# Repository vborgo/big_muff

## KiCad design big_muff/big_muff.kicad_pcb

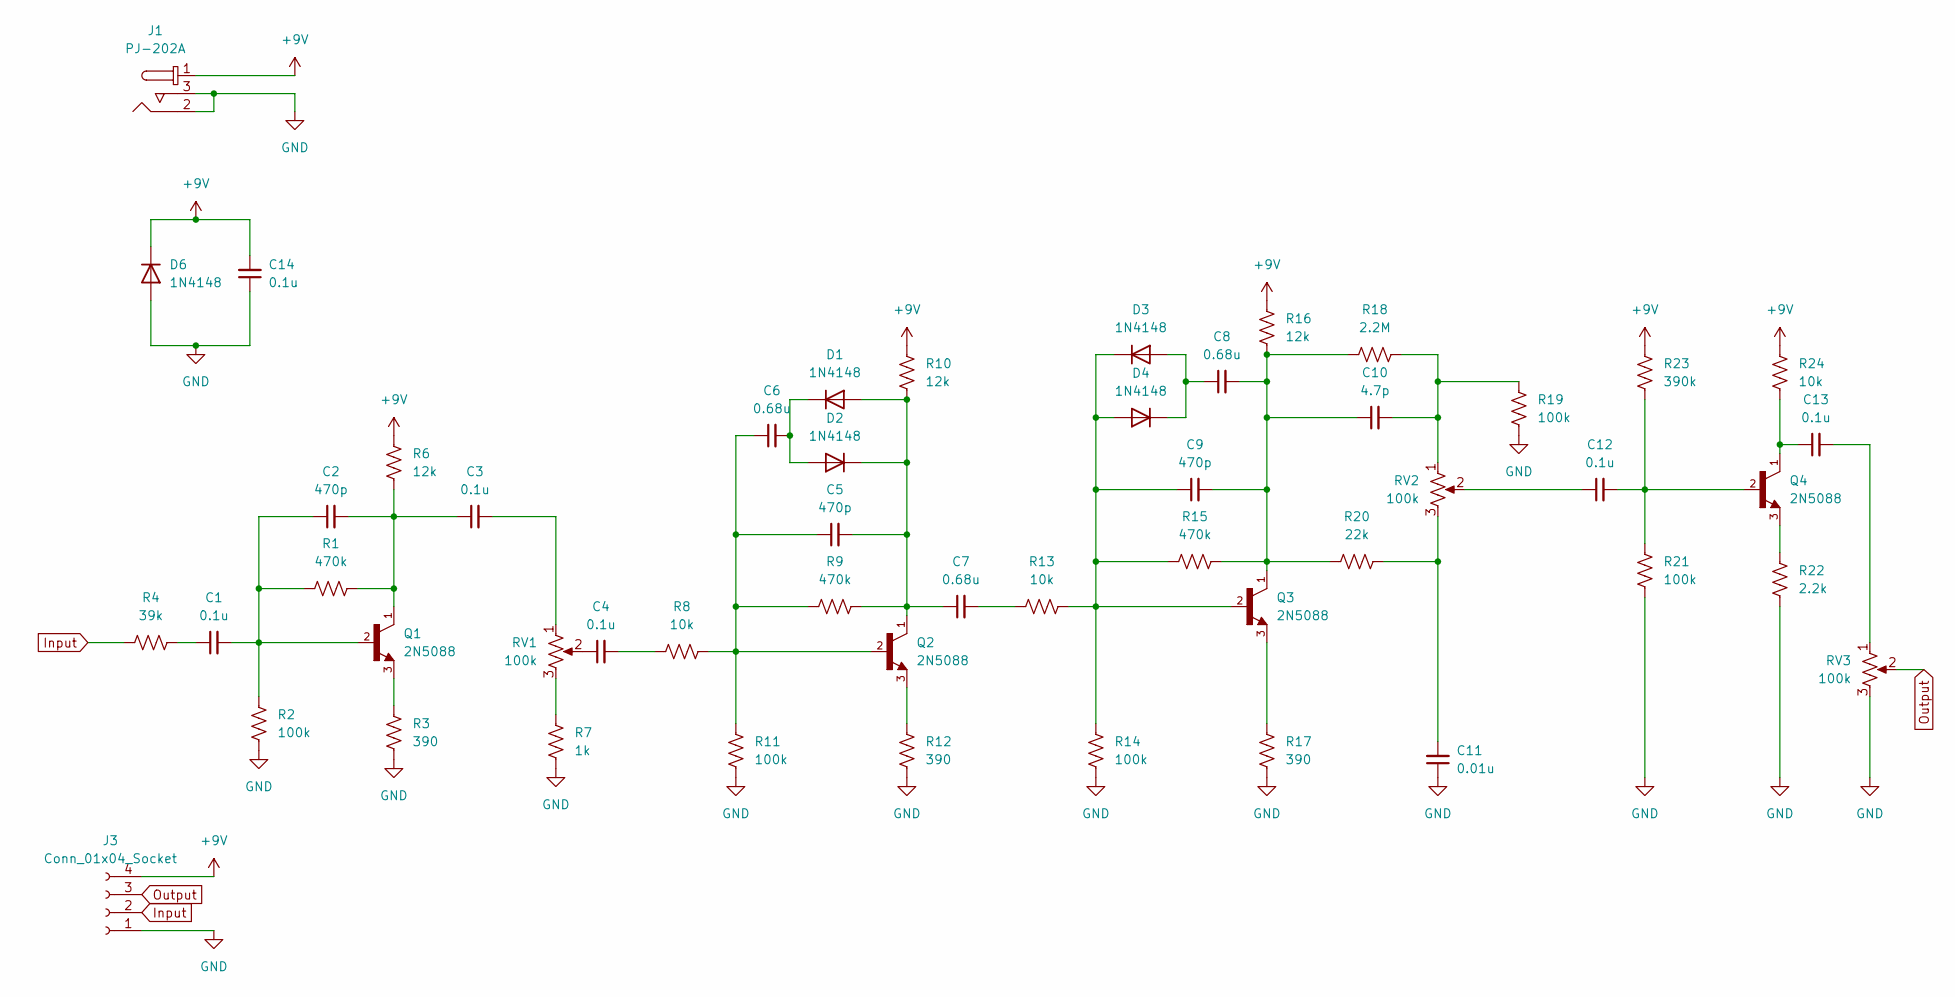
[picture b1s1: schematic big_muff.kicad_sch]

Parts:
C1, C3, C4, C12, C13, C14: 0.1u; C_Axial_L5.1mm_D3.1mm_P7.50mm_Horizontal
C2, C5, C9: 470p; C_Axial_L5.1mm_D3.1mm_P7.50mm_Horizontal
C6, C7, C8: 0.68u; C_Axial_L5.1mm_D3.1mm_P7.50mm_Horizontal
C10: 4.7p; C_Axial_L5.1mm_D3.1mm_P7.50mm_Horizontal
C11: 0.01u; C_Axial_L5.1mm_D3.1mm_P7.50mm_Horizontal
D1, D2, D3, D4, D6: 1N4148; D_DO-35_SOD27_P7.62mm_Horizontal
J1: PJ-202A; BarrelJack_GCT_DCJ200-10-A_Horizontal; MPN PJ-202A; Digi-Key_PN CP-202A-ND
J3: Conn_01x04_Socket; PinHeader_1x04_P2.00mm_Vertical
Q1, Q2, Q3, Q4: 2N5088; TO92
R1, R9, R15: 470k; R_Axial_DIN0204_L3.6mm_D1.6mm_P5.08mm_Horizontal
R2, R11, R14, R19, R21: 100k; R_Axial_DIN0204_L3.6mm_D1.6mm_P5.08mm_Horizontal
R3, R12, R17: 390; R_Axial_DIN0204_L3.6mm_D1.6mm_P5.08mm_Horizontal
R4: 39k; R_Axial_DIN0204_L3.6mm_D1.6mm_P5.08mm_Horizontal
R6, R10, R16: 12k; R_Axial_DIN0204_L3.6mm_D1.6mm_P5.08mm_Horizontal
R7: 1k; R_Axial_DIN0204_L3.6mm_D1.6mm_P5.08mm_Horizontal
R8, R13, R24: 10k; R_Axial_DIN0204_L3.6mm_D1.6mm_P5.08mm_Horizontal
R18: 2.2M; R_Axial_DIN0204_L3.6mm_D1.6mm_P5.08mm_Horizontal
R20: 22k; R_Axial_DIN0204_L3.6mm_D1.6mm_P5.08mm_Horizontal
R22: 2.2k; R_Axial_DIN0204_L3.6mm_D1.6mm_P5.08mm_Horizontal
R23: 390k; R_Axial_DIN0204_L3.6mm_D1.6mm_P5.08mm_Horizontal
RV1, RV2, RV3: 100k; Potentiometer_Bourns_PTV09A-1_Single_Vertical

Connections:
+9V: C14.2, D6.1 (K), J1.1, J3.4, R6.1, R10.2, R16.2, R23.1, R24.1
GND: C11.1, C14.1, D6.2 (A), J1.2, J1.3, J3.1, R2.2, R3.2, R7.2, R11.1, R12.1, R14.1, R17.1, R19.2, R21.2, R22.2, RV3.3
Input: J3.2, R4.2
unnamed: C1.1, R4.1
unnamed: C1.2, C2.1, Q1.2, R1.2, R2.1
unnamed: C2.2, C3.1, Q1.1, R1.1, R6.2
unnamed: C3.2, RV1.1
unnamed: C4.1, RV1.2
unnamed: C4.2, R8.1
unnamed: C5.1, C6.1, Q2.2, R8.2, R9.1, R11.2
unnamed: C7.2, R13.1
unnamed: C8.2, C9.2, C10.1, Q3.1, R15.2, R16.1, R18.2, R20.2
unnamed: C10.2, R18.1, R19.1, RV2.1
unnamed: C11.2, R20.1, RV2.3
unnamed: C12.1, RV2.2
unnamed: C12.2, Q4.2, R21.1, R23.2
unnamed: C13.1, Q4.1, R24.2
unnamed: C13.2, RV3.1
unnamed: C5.2, C7.1, D1.2 (A), D2.1 (K), Q2.1, R9.2, R10.1
unnamed: C6.2, D1.1 (K), D2.2 (A)
unnamed: C8.1, D3.2 (A), D4.1 (K)
unnamed: C9.1, D3.1 (K), D4.2 (A), Q3.2, R13.2, R14.2, R15.1
unnamed: Q1.3, R3.1
unnamed: Q2.3, R12.2
unnamed: Q3.3, R17.2
unnamed: Q4.3, R22.1
unnamed: R7.1, RV1.3
Output: J3.3, RV3.2

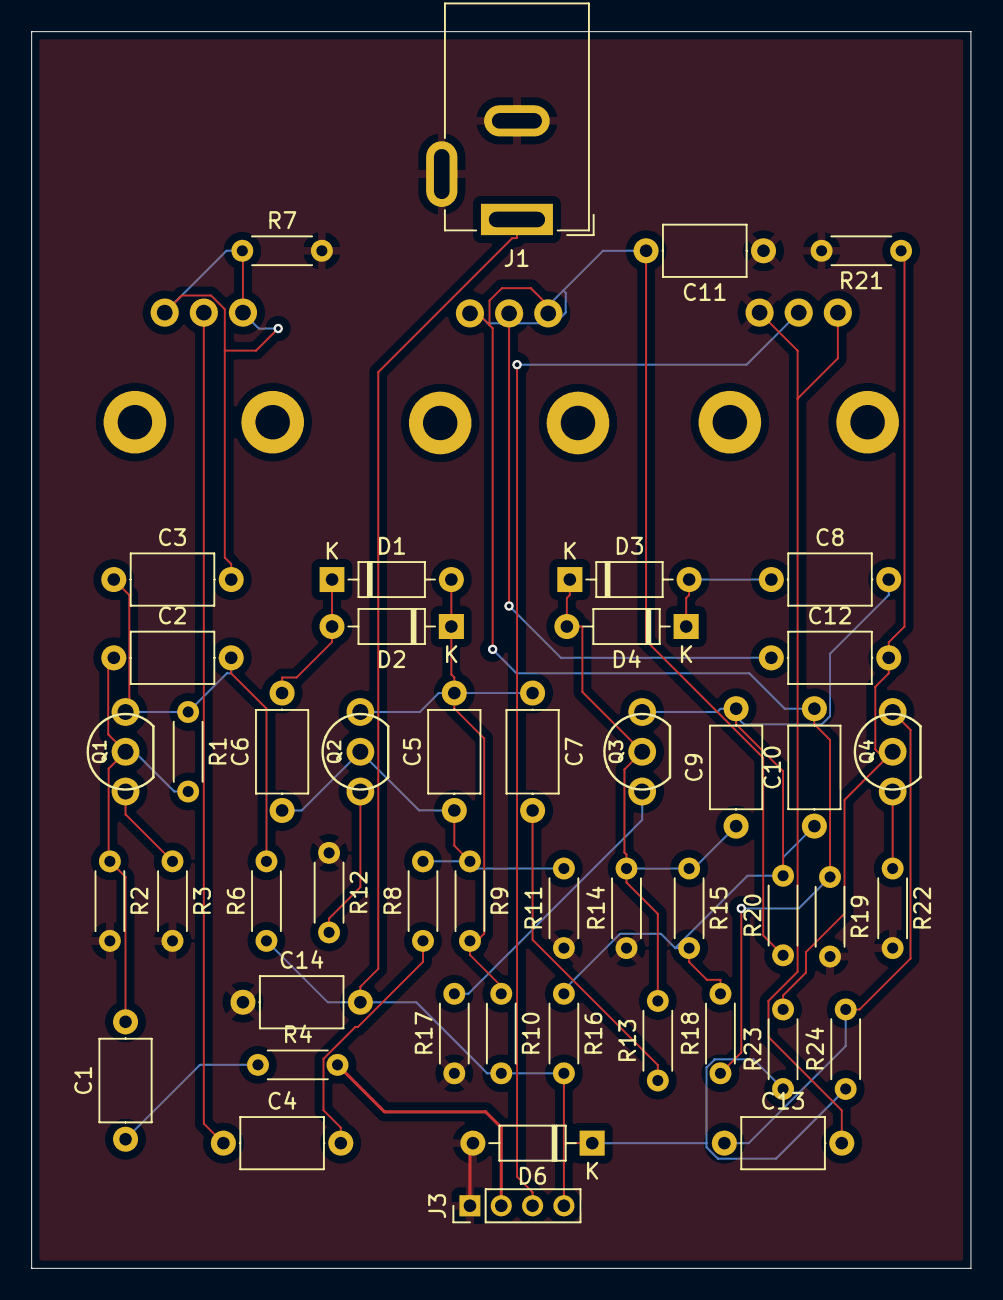
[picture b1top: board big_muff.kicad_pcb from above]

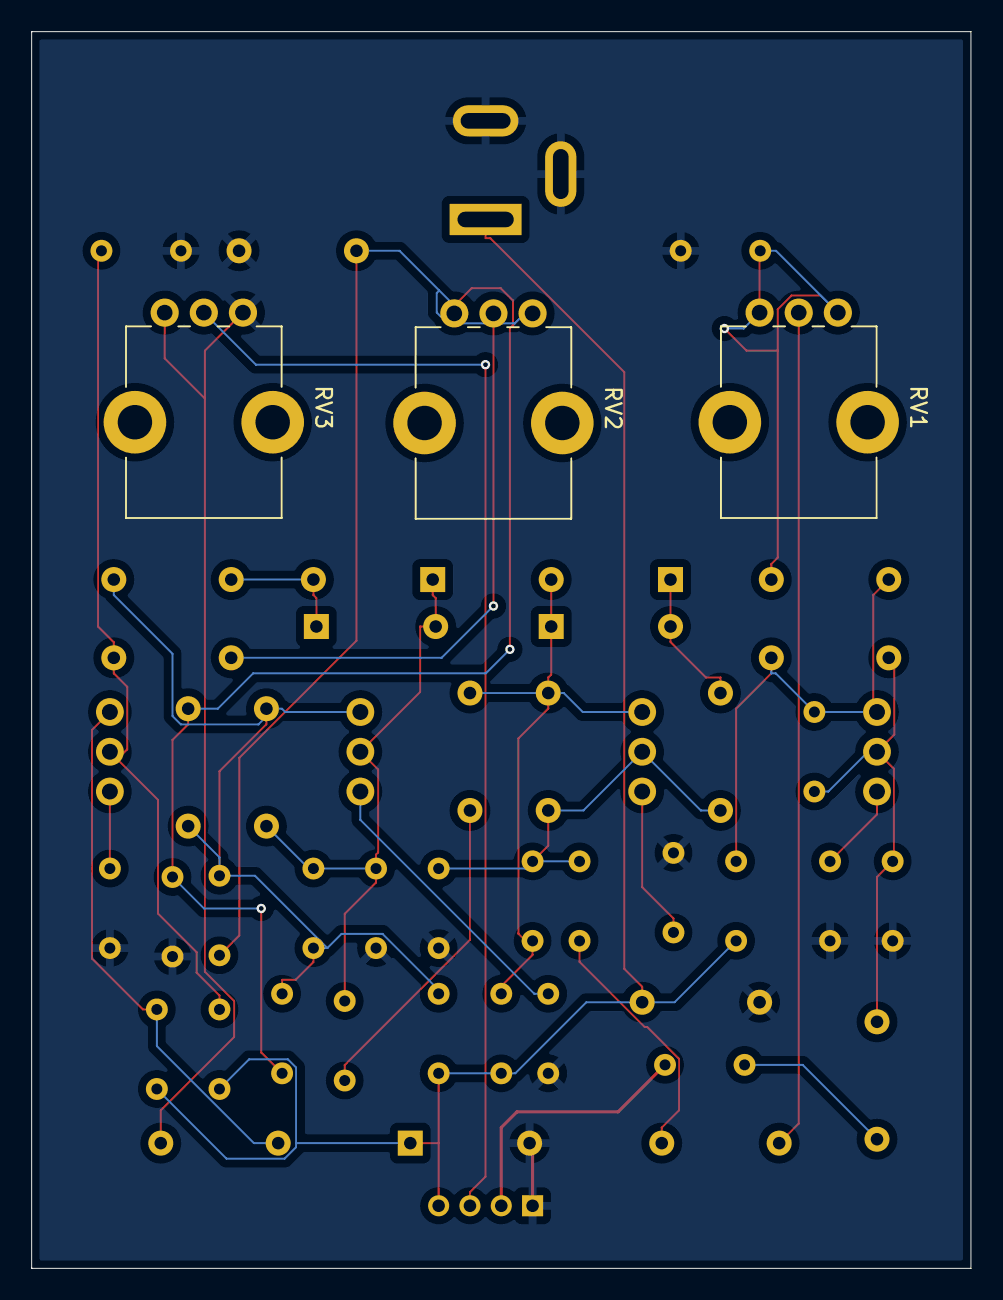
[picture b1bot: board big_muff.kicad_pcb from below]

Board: 2 copper layers, 60.0 x 79.0 mm, 51 parts (3 on the bottom side), 28 nets.

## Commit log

2025-03-16 Add git ignore file
2025-03-16 First commit for files of Big Muff project
2026-01-22 Continue work with big muff
2026-01-22 Add .opencode as submodule
    From: https://github.com/vborgo/.opencode.git
2026-01-24 Remove duplicated project folder in two levels
